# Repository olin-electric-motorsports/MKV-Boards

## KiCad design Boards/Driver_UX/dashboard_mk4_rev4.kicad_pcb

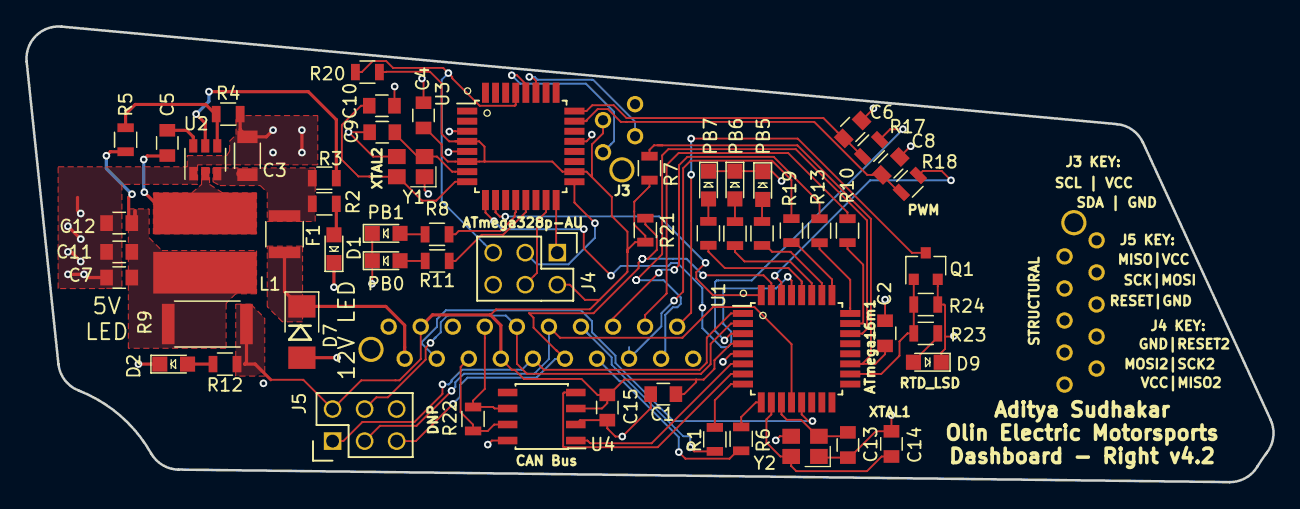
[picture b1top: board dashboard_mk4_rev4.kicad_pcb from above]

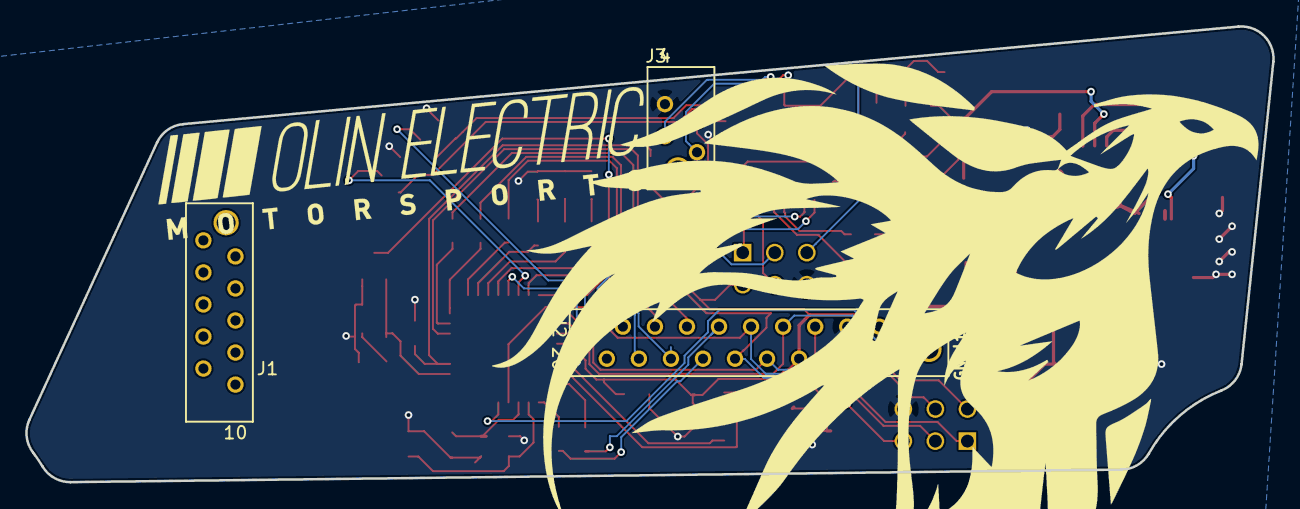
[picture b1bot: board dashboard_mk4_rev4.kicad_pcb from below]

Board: 2 copper layers, 98.8 x 36.1 mm, 62 parts (3 on the bottom side), 61 nets.

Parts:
C1, C4, C5, C6, C7, C8, C15: C_0.1uF; C_0805_OEM
C2: C_100pF; C_0805_OEM
C3: C_22uF; C_1206_OEM
C9, C10, C13, C14: C_30pF; C_0805_OEM
C11: C_1uF; C_0805_OEM
C12: C_47uF; C_0805_OEM
D1, D2: LED_0805; LED_0805_OEM
D7: D_Zener_18V; DO-214AA
D9: LED; LED_0805_OEM
F1: 500mA; Fuse_1210
J1: MM_F_VT_10; micromatch_female_vert_10
J2: MM_F_VT_20; micromatch_female_vert_20
J3: MM_F_VT_04; micromatch_female_vert_4
J4, J5: CONN_02X03; Pin_Header_Straight_2x03
L1: L_4.7uH; 4.7uH_Inductor_OEM
PB0, PB1, PB5, PB6, PB7: LED; LED_0805_OEM
Q1: SSM3K333R; SOT-23F
R1, R6, R8, R10, R11, R12, R13, R14, R15, R16, R19, R23: R_200; R_0805_OEM
R2: R_1k; R_0805_OEM
R3, R4, R21: R_10k; R_0805_OEM
R5: R_51.1k; R_0805_OEM
R7: R_100; R_0805_OEM
R9: R_0_Jumper; R_2512_OEM
R17, R18: R_100K; R_0805_OEM
R20: R_10K; R_0805_OEM
R22: R_120; R_0805_OEM
R24: R_100k; R_0805_OEM
U1: ATMEGA16M1; TQFP-32_7x7mm_Pitch0.8mm
U2: TPS561201; SOT-23-6_OEM
U3: ATmega328P-AU_FORMULA_MK4; TQFP-32_7x7mm_Pitch0.8mm
U4: CAN_Transceiver; SOIC-8_3.9x4.9mm_Pitch1.27mm_OEM
Y1, Y2: Crystal_SMD; Crystal_SMD_FA238

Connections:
+12V: D7.1, F1.1, J2.2
/12V_Fused: C3.1, F1.2, R2.1, R3.1, U2.3
/CANH: J2.6, R22.1, U4.7
/CANL: J2.7, R22.2, U4.6
/INFO1: U1.29, U3.9
/INFO2: U1.32, U3.10
/LED_BMS: J2.16, R19.2
/LED_IMD: J2.17, R10.1
/LED_START: J2.15, R13.1
/MISO: J2.10, J5.1, U1.1
/MISO_2: J4.1, U3.16
/MOSI: J2.9, J5.4, U1.2
/MOSI_2: J4.4, U3.15
/PWM_0: R18.1, U1.30
/PWM_1: R17.1, U1.3
/RESET: J2.12, J5.5, R21.1, U1.31
/RESET_2: J4.5, R20.1, U3.29
/RJLED1: J2.13, R1.1
/RJLED2: J2.14, R6.1
/RTD_BUZZER: J2.19, Q1.3
/RXCAN: U1.7, U4.4
/SCK: J2.11, J5.3, U1.12
/SCK_2: J4.3, U3.17
/SCL: J3.1, U3.28
/SDA: J3.2, U3.27
/START_BTN: J2.18, U1.22
/STR_POT_SENSE: J2.4, U1.13
/TXCAN: U1.6, U4.1
/XTAL1: C9.1, U3.7, Y1.1
/XTAL2: C10.1, U3.8, Y1.3
GND: C1.2, C2.2, C3.2, C4.2, C6.2, C7.2, C8.2, C9.2, C10.2, C11.2, C12.2, C13.2, C14.2, C15.2, D1.1, D2.1, D7.2, D9.1, J2.1, J2.5, J3.4, J4.6, J5.6, PB0.1, PB1.1, PB5.1, PB6.1, PB7.1, Q1.2, R4.2, R24.2, U1.5, U2.1, U3.3, U3.5, U3.21, U4.2, U4.8, Y1.2, Y1.4, Y2.2, Y2.4
unnamed: C2.1, R7.2, U1.19
unnamed: C5.1, U2.6
unnamed: C5.2, L1.1, U2.2
unnamed: C6.1, R17.2, U3.24
unnamed: C8.1, R18.2, U3.23
unnamed: C7.1, C11.1, C12.1, L1.2, R5.2, R9.2
unnamed: C13.1, U1.11, Y2.1
unnamed: C14.1, U1.10, Y2.3
unnamed: D1.2, R2.2
unnamed: D2.2, R12.2
unnamed: PB1.2, R8.1
unnamed: PB0.2, R11.1
unnamed: PB5.2, R14.2
unnamed: PB6.2, R15.2
unnamed: PB7.2, R16.2
unnamed: D9.2, R23.2
unnamed: Q1.1, R23.1, R24.1, U1.18
unnamed: R1.2, U1.8
unnamed: R3.2, U2.5
unnamed: R4.1, R5.1, U2.4
unnamed: R6.2, U1.9
unnamed: R8.2, U3.12
unnamed: R10.2, U1.23
unnamed: R11.2, U3.13
unnamed: R13.2, U1.24
unnamed: R14.1, U1.26
unnamed: R15.1, U1.27
unnamed: R16.1, U1.28
unnamed: R19.1, U1.25
VCC: C1.1, C4.1, C15.1, J2.3, J2.8, J3.3, J4.2, J5.2, R7.1, R9.1, R12.1, R20.2, R21.2, U1.4, U3.4, U3.6, U3.18, U4.3

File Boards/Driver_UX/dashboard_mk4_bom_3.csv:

Component,Description,Part,References,Value,Footprint,Quantity Per PCB,Datasheet,Package,MPN,MFN,PurchasingLink
1,"Capacitor, 0.1uF, 50V, 5%, 0805",C_0.1uF,C1 C4 C5 C6 C7 C8 C15,C_0.1uF,C_0805_OEM,7,http://datasheets.avx.com/X7RDielectric.pdf,Value,478-3352-1-ND,DK,https://www.digikey.com/products/en?keywords=478-3352-1-ND
2,"Capacitor, 100pF, 50V, 5%, 0805",C_100pF,C2,C_100pF,C_0805_OEM,1,https://katalog.we-online.de/pbs/datasheet/885012007057.pdf,Value,732-7852-1-ND,DK,https://www.digikey.com/product-detail/en/wurth-electronics-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
3,"Capacitor, 1uF, 25V, 10%, 0805",C_1uF,C11,C_1uF,C_0805_OEM,1,http://www.samsungsem.com/kr/support/product-search/mlcc/__i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,Value,1276-2887-1-ND,DK,https://www.digikey.com/product-detail/en/samsung-electro-me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
4,"Capacitor, 22uF, 16V, 20%, 1206",C_22uF,C3,C_22uF,C_1206_OEM,1,https://product.tdk.com/info/en/catalog/datasheets/mlcc_comm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,Value,445-11693-1-ND,DK,https://www.digikey.com/product-detail/en/tdk-corporation/C3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
5,"Capacitor, 30pF, 50V, 5%, 0805",C_30pF,C9 C10 C13 C14,C_30pF,C_0805_OEM,4,https://media.digikey.com/pdf/Data%20Sheets/Samsung%20PDFs/C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,Value,1276-1130-1-ND,DK,https://www.digikey.com/product-detail/en/samsung-electro-me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
6,"Capacitor, 47uF, 6.3V, 20%, 0805",C_47uF,C12,C_47uF,C_0805_OEM,1,http://www.samsungsem.com/kr/support/product-search/mlcc/__i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,Value,1276-6467-1-ND,DK,https://www.digikey.com/product-detail/en/samsung-electro-me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
7,"Diode, Zener, 18V, 5W, 5%",D_Zener_18V,D7,D_Zener_18V,DO-214AA,1,http://www.mccsemi.com/up_pdf/SMBJ5338B-SMBJ5388B(SMB).pdf,DO-214AA (SMB),SMBJ5355B-TPMSCT-ND,DK,https://www.digikey.com/products/en?keywords=SMBJ5355B-TPMSCT-ND
8,Light emitting diode,LED,D3 D4 D5 D6 D8,LED,LED_0805_OEM,5,,,,,
9,Light emitting diode,LED,D9,LED,LED_0805_OEM,1,~,,,,
10,"LED, Green, 2.2V, 20mA, 0805",LED_0805,D1 D2,LED_0805,LED_0805_OEM,2,http://www.osram-os.com/Graphics/XPic9/00078860_0.pdf,Value,475-1410-1-ND,DK,https://www.digikey.com/products/en?keywords=475-1410-1-ND
11,"Fuse, PTC, 500mA, 16V, 1210",F_500mA_16V,F1,500mA,Fuse_1210,1,https://belfuse.com/resources/CircuitProtection/datasheets/0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,Value,507-1786-1-ND,DK,https://www.digikey.com/product-detail/en/bel-fuse-inc/0ZCH0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
12,"Connector header through hole 2x3 0.100"" (2.54mm)",CONN_02X03,J4 J5,CONN_02X03,Pin_Header_Straight_2x03,2,http://portal.fciconnect.com/Comergent//fci/drawing/67996.pdf,Value,609-3234-ND,DK,https://www.digikey.com/product-detail/en/amphenol-fci/67997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
13,Micro-MaTch connector 4 pin female vertical,MM_F_VT_04,J3,MM_F_VT_04,micromatch_female_vert_4,1,http://www.te.com/commerce/DocumentDelivery/DDEController?Ac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,,338068-4,TE,http://www.te.com/global-en/product-338068-4.html
14,Micro-MaTch connector 10 pin female vertical,MM_F_VT_10,J1,MM_F_VT_10,micromatch_female_vert_10,1,http://www.te.com/commerce/DocumentDelivery/DDEController?Ac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,,1-338068-0,TE,http://www.te.com/global-en/product-1-338068-0.html
15,Micro-MaTch connector 20 pin female vertical,MM_F_VT_20,J2,MM_F_VT_20,micromatch_female_vert_20,1,http://www.te.com/commerce/DocumentDelivery/DDEController?Ac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,,2-338068-0,TE,http://www.te.com/global-en/product-2-338068-0.html
16,"Inductor, 4.7uH, 4.4A, 25mOhm, 20%",L_4.7uH,L1,L_4.7uH,4.7uH_Inductor_OEM,1,https://product.tdk.com/info/en/documents/wdcatalog/withdraw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,Value,445-6583-1-ND,DK,https://www.digikey.com/product-detail/en/tdk-corporation/VL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
17,"MOSFET, N-channel, 30V, 6A",SSM3K333R,Q1,SSM3K333R,SOT-23F,1,https://drive.google.com/drive/folders/0B-V-iZf33Y4GNzhDQTJZanJRbVk,,SSM3K333RLFCT-ND,DK,https://www.digikey.com/product-detail/en/toshiba-semiconduc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
18,"Resistor, 0 ohm jumper, 0.1W, 0603",R_0,R9,R_0_Jumper,R_0603_1608Metric,1,http://industrial.panasonic.com/www-cgi/jvcr13pz.cgi?E+PZ+3+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,Value,P0.0GCT-ND,DK,https://www.digikey.com/product-detail/en/panasonic-electron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
19,"Resistor, 100, 0.25W, 1%, 0805",R_100,R7,R_100,R_0805_OEM,1,https://www.seielect.com/Catalog/SEI-rncp.pdf,Value,RNCP0805FTD100RCT-ND,DK,https://www.digikey.com/products/en?keywords=RNCP0805FTD100RCT-ND
20,"Resistor, 100K, 0.125W, 1%, 0805",R_100K,R17 R18,R_100K,R_0805_OEM,2,https://industrial.panasonic.com/cdbs/www-data/pdf/RDA0000/A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,,P100KCCT-ND,DK,https://www.digikey.com/product-detail/en/panasonic-electron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
21,Resistor,R,R24,R_100k,R_0805_OEM,1,~,,,,
22,"Resistor, 10K, 0.25W, 1%, 0805",R_10K,R20 R21,R_10K,R_0805_OEM,2,http://www.bourns.com/data/global/pdfs/CRS.pdf,Value,CRS0805-FX-1002ELFCT-ND,DK,https://www.digikey.com/products/en?keywords=CRS0805-FX-1002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
23,"Resistor, 10K, 5W, 1%, Axial",R_10K_HV,R3 R4,R_10k,R_1K_HV,2,http://www.vishay.com/docs/28731/pacserie.pdf,Value,PPC5D10.0KCT-ND,DK,https://www.digikey.com/products/en?keywords=PPC5D10.0KCT-ND
24,"Resistor, 200, 0.125W, 5%, 0805",R_200,R22,R_120,R_0805_OEM,1,https://www.seielect.com/Catalog/SEI-RMCF_RMCP.pdf,Value,RMCF0805JT200RCT-ND,DK,https://www.digikey.com/products/en?keywords=RMCF0805JT200RCT-ND
25,"Resistor, 1K, 0.25W, 1%, 0805",R_1K,R2,R_1k,R_0805_OEM,1,https://www.seielect.com/Catalog/SEI-rncp.pdf,Value,RNCP0805FTD1K00CT-ND,DK,https://www.digikey.com/products/en?keywords=RNCP0805FTD1K00CT-ND
26,"Resistor, 200, 0.125W, 5%, 0805",R_200,R1 R6 R8 R10 R11 R12 R13 R14 R15 R16 R19,R_200,R_0805_OEM,11,https://www.seielect.com/Catalog/SEI-RMCF_RMCP.pdf,Value,RMCF0805JT200RCT-ND,DK,https://www.digikey.com/products/en?keywords=RMCF0805JT200RCT-ND
27,Resistor,R,R23,R_200,R_0805_OEM,1,~,,,,
28,"Resistor, 51.1K, 0.125W, 1%, 0805",R_51.1K,R5,R_51.1k,R_0805_OEM,1,https://industrial.panasonic.com/cdbs/www-data/pdf/RDA0000/A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,Value,P51.1KCCT-ND,DK,https://www.digikey.com/product-detail/en/panasonic-electron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
29,"Microcontroller, 8-bit, 1KB RAM, 16KB Flash",ATMEGA16M1,U1,ATMEGA16M1,TQFP-32_7x7mm_Pitch0.8mm,1,http://ww1.microchip.com/downloads/en/DeviceDoc/Atmel-8209-8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,,ATMEGA16M1-AU-ND,DK,https://www.digikey.com/product-detail/en/atmel/ATMEGA16M1-A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
30,"High speed CAN transceiver, 1Mb/s",MCP2561-E_SN,U4,CAN_Transceiver,SOIC-8_3.9x4.9mm_Pitch1.27mm_OEM,1,http://www.microchip.com/mymicrochip/filehandler.aspx?ddocna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,Value,MCP2561-E/SN-ND,DK,https://www.digikey.com/products/en?keywords=mcp2561-e%2Fsn
31,"Buck converter, 4.5-17V input, adj 0.76-7V output, 1A, 580kHz",TPS561201,U2,TPS561201,SOT-23-6_OEM,1,http://www.ti.com/lit/ds/symlink/tps561201.pdf,Value,TPS561201,DK,https://www.digikey.com/products/en?keywords=296-46928-1-ND
32,CRYSTAL 16.0000MHZ 18PF SMD,Crystal_SMD,Y1 Y2,Crystal_SMD,Crystal_SMD_FA238,2,http://www.txccorp.com/download/products/quartz_crystals/201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,Value,887-1125-1-ND,DK,https://www.digikey.com/product-detail/en/txc-corporation/7M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





Component Groups:,32
Component Count:,61
Fitted Components:,61
Number of PCBs:,1
Total components:,61
Schematic Version:,3
Schematic Date:,
BoM Date:,Sun 24 Feb 2019 12:24:09 PM EST
Schematic Source:,/home/asudhakar/Documents/Forumla/MKIV-Boards/Boards/Dashboard Mk4/rev4/dashboard_mk4.sch
KiCad Version:,Eeschema 5.0.2-bee76a0~70~ubuntu18.04.1

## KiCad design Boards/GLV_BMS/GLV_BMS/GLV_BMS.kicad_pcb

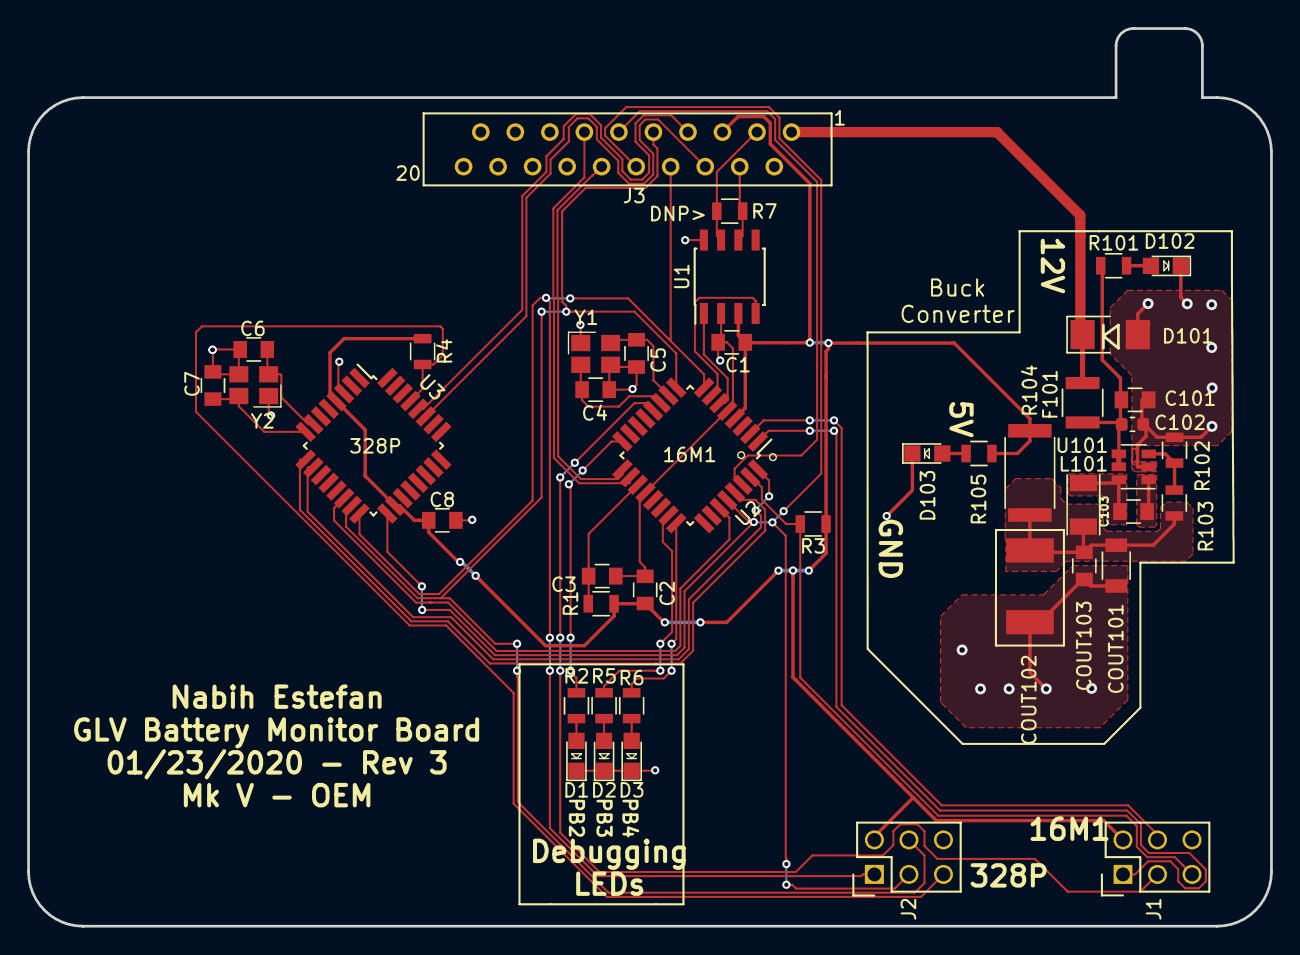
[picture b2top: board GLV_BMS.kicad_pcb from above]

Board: 2 copper layers, 91.4 x 66.0 mm, 43 parts (0 on the bottom side), 41 nets.

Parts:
C1, C2, C8, C101, C103: C_0.1uF; C_0805_OEM
C3: C_100pF; C_0805_OEM
C4, C5, C6, C7: C_30pF; C_0805_OEM
C102: C_2.2uF; C_0603_1608Metric
COUT101: C_22uF; C_1206_OEM
COUT102: C_33uF; Fuse_1812
COUT103: C_47uF; C_0805_OEM
D1, D2, D3, D102, D103: LED_0805; LED_0805_OEM
D101: D_Zener_18V; DO-214AA
F101: F_500mA_16V; Fuse_1210
J1, J2: CONN_02X03; Pin_Header_Straight_2x03
J3: MM_F_RA_20; micromatch_female_ra_20
L101: L_100uH; L_100uH_OEM
R1: R_100; R_0805_OEM
R2, R5, R6, R105: R_200; R_0805_OEM
R3, R4: R_10K; R_0805_OEM
R7: R_120_DNP; R_0805_OEM
R101: R_1K; R_0805_OEM
R102: R_25K; R_0805_OEM
R103: R_100K; R_0805_OEM
R104: R_0_2512; R_2512_OEM
U1: MCP2561-E_SN; SOIC-8_3.9x4.9mm_Pitch1.27mm_OEM
U2: ATMEGA16M1; TQFP-32_7x7mm_Pitch0.8mm
U3: ATmega328P-AU; TQFP-32_7x7mm_P0.8mm
U101: TPS560430YF; SOT-23-6_OEM
Y1, Y2: Crystal_SMD; Crystal_SMD_FA238

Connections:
+12V: D101.1, F101.2, J3.1
/ALERT_COOLING: J3.13, U2.18
/ALERT_GLV: J3.12, U2.17
/CAN_HI: J3.3, R7.1, U1.7
/CAN_LO: J3.4, R7.2, U1.6
/CAN_RX: U1.4, U2.7
/CAN_TX: U1.1, U2.6
/CS_2: U2.27, U3.14
/CS_GLV: J3.11, U2.30
/INFO1: U2.29, U3.9
/INFO2: U2.32, U3.10
/LED_1: R2.2, U2.16
/LED_2: R5.2, U2.23
/LED_3: R6.2, U2.24
/MISO: J1.1, U2.1
/MISO_2: J2.1, J3.8, U2.8, U3.16
/MOSI: J1.4, U2.2
/MOSI_2: J2.4, J3.9, U2.9, U3.15
/RESET: J1.5, R3.2, U2.31
/RESET_2: J2.5, R4.2, U3.29
/SCK: J1.3, U2.12
/SCK_2: J2.3, J3.10, U2.28, U3.17
/SCL: J3.7, U3.28
/SDA: J3.6, U3.27
/XTAL1: C4.1, U2.11, Y1.1
/XTAL1_2: C6.1, U3.7, Y2.1
/XTAL2: C5.1, U2.10, Y1.3
/XTAL2_2: C7.1, U3.8, Y2.3
GND: C1.2, C2.2, C3.2, C4.2, C5.2, C6.2, C7.2, C8.2, C101.2, C102.2, COUT101.2, COUT102.2, COUT103.2, D1.1, D2.1, D3.1, D101.2, D102.1, D103.1, J1.6, J2.6, J3.2, J3.14, J3.15, J3.16, J3.17, J3.18, J3.19, J3.20, R102.2, U1.2, U1.8, U2.5, U2.20, U3.3, U101.2, Y1.2, Y1.4, Y2.2, Y2.4
unnamed: C3.1, R1.2, U2.19
unnamed: C101.1, C102.1, F101.1, R101.1, U101.4, U101.5
unnamed: C103.1, U101.1
unnamed: C103.2, L101.1, U101.6
unnamed: COUT101.1, COUT102.1, COUT103.1, L101.2, R103.1, R104.1
unnamed: D1.2, R2.1
unnamed: D2.2, R5.1
unnamed: D3.2, R6.1
unnamed: D102.2, R101.2
unnamed: D103.2, R105.2
unnamed: R102.1, R103.2, U101.3
VCC: C1.1, C2.1, C8.1, J1.2, J2.2, J3.5, R1.1, R3.1, R4.1, R104.2, R105.1, U1.3, U2.4, U3.4, U3.18

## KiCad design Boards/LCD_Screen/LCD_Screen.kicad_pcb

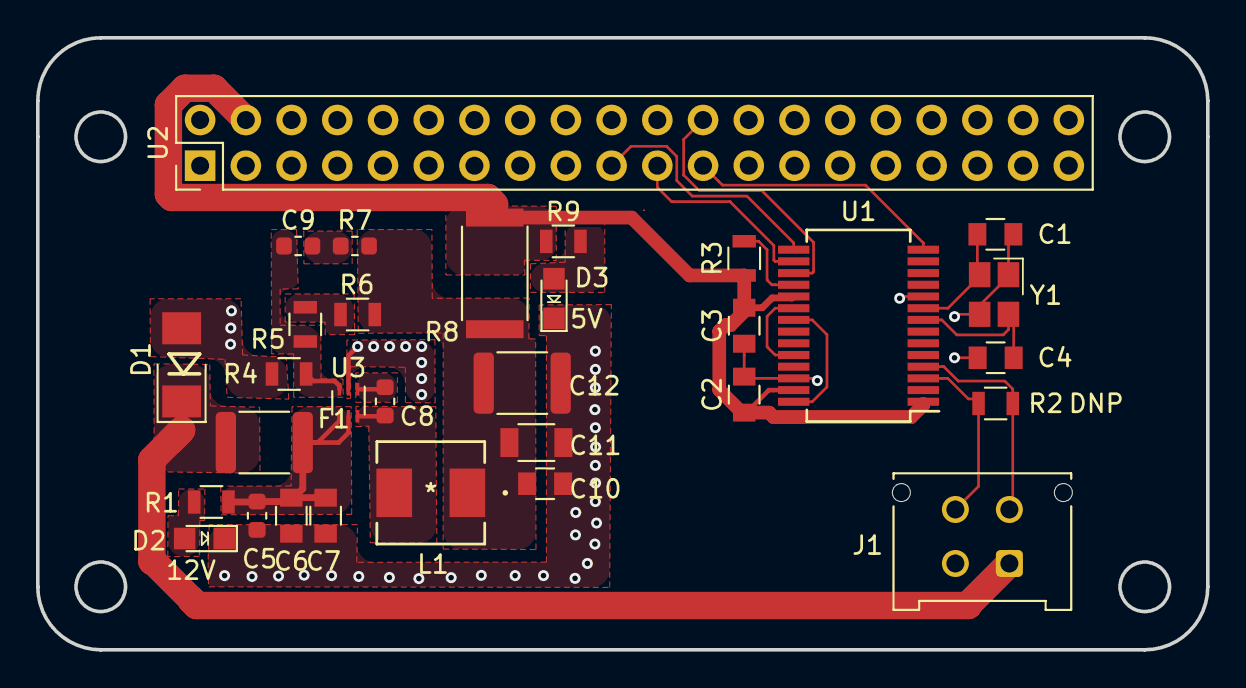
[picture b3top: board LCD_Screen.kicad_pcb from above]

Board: 2 copper layers, 65.0 x 34.0 mm, 31 parts (0 on the bottom side), 23 nets.

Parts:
C1, C4: C_30pF; C_0805_OEM
C2: C_0.1uF; C_0805_OEM
C3: C_100pF; C_0805_OEM
C5: C_0.1uF; C_0603_1608Metric
C6, C7: C_10uF_25V; C_0805_OEM
C8: C_0.1uF_0603; C_0603_1608Metric
C9: C_100nF; C_0603_1608Metric
C10: C_10uF; C_0805_OEM
C11: C_22uF; C_1206_OEM
C12: C_33uF; C_1812_4532Metric
D1: D_Zener_18V; DO-214AA
D2, D3: LED_0805; LED_0805_OEM
F1: F_2.6A_16V; Fuse_1812_4532Metric
J1: MicroFit_VT_4
L1: L_4.7uH_3.2A; IHLP2020BZER4R7M11
R1: R_1K; R_0805_OEM
R2: R_120_DNP; R_0805_OEM
R3, R4: R_10K; R_0805_OEM
R5: R_51.1K; R_0805_OEM
R6: R_22K; R_0805_OEM
R7: R_1; R_0603_1608Metric
R8: R_0_2512; R_2512_OEM
R9: R_200; R_0805_OEM
U1: MCP25625-x-SS; SSOP-28_5.3x10.2mm_P0.65mm
U2: Raspberry_Pi_Zero; PinHeader_2x20_P2.54mm_Vertical
U3: TPS563231; SOT-563
Y1: Crystal_SMD; Crystal_SMD_FA238

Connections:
/12V: D1.1, F1.1, J1.1
/CANH: J1.3, R2.1, U1.4
/CANL: J1.4, R2.2, U1.3
/MISO: U1.16, U2.21
/MOSI: U1.15, U2.19
/SCK: U1.14, U2.23
/~CS~: U1.17, U2.24
GND: C1.2, C2.2, C3.2, C4.2, C5.2, C6.2, C7.2, C10.2, C11.2, C12.2, D1.2, D2.1, D3.1, J1.2, R4.2, U1.10, U1.26, U2.39, U3.2, Y1.2, Y1.4
unnamed: C1.1, U1.9, Y1.1
unnamed: C4.1, U1.8, Y1.3
unnamed: C5.1, C6.1, C7.1, F1.2, R1.1, U3.4, U3.5
unnamed: C8.1, L1.2, U3.6
unnamed: C8.2, U3.1
unnamed: C9.1, R4.1, R5.2, U3.3
unnamed: C9.2, R7.1
unnamed: C10.1, C11.1, C12.1, L1.1, R6.1, R7.2, R8.2
unnamed: D2.2, R1.2
unnamed: D3.2, R9.2
unnamed: R3.1, U1.18
unnamed: R5.1, R6.2
unnamed: U1.20, U1.24
unnamed: U1.21, U1.28
VCC: C2.1, C3.1, R3.2, R8.1, R9.1, U1.1, U1.19, U1.27, U2.4

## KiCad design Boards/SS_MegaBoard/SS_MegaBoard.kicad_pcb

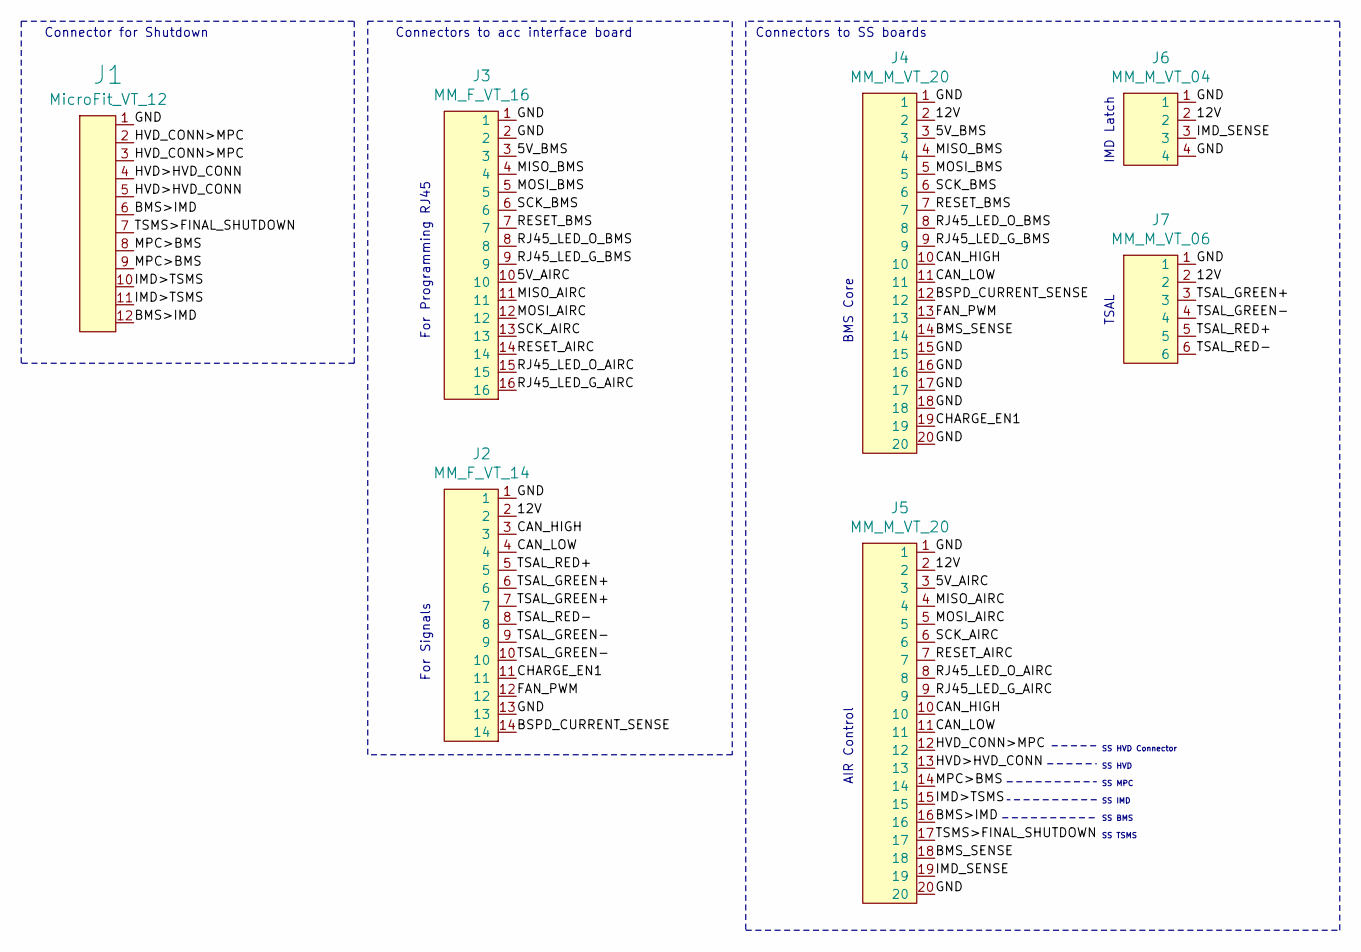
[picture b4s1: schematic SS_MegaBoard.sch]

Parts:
J1: MicroFit_VT_12
J2: MM_F_VT_14; micromatch_female_vert_14; MPN 1-338068-4
J3: MM_F_VT_16; micromatch_female_vert_16; MPN 1-338068-6
J4, J5: MM_M_VT_20; micromatch_female_vert_20; MPN 2-215464-0
J6: MM_M_VT_04; micromatch_female_vert_4; MPN 215464-4
J7: MM_M_VT_06; micromatch_female_vert_6; MPN 215464-6

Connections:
/5V_AIRC: J3.10, J5.3
/5V_BMS: J3.3, J4.3
/12V: J2.2, J4.2, J5.2, J6.2, J7.2
/BMS>IMD: J1.6, J1.12, J5.16
/BMS_SENSE: J4.14, J5.18
/BSPD_CURRENT_SENSE: J2.14, J4.12
/CAN_HIGH: J2.3, J4.10, J5.10
/CAN_LOW: J2.4, J4.11, J5.11
/CHARGE_EN1: J2.11, J4.19
/FAN_PWM: J2.12, J4.13
/GND: J1.1, J2.1, J2.13, J3.1, J3.2, J4.1, J4.15, J4.16, J4.17, J4.18, J4.20, J5.1, J5.20, J6.1, J6.4, J7.1
/HVD>HVD_CONN: J1.4, J1.5, J5.13
/HVD_CONN>MPC: J1.2, J1.3, J5.12
/IMD>TSMS: J1.10, J1.11, J5.15
/IMD_SENSE: J5.19, J6.3
/MISO_AIRC: J3.11, J5.4
/MISO_BMS: J3.4, J4.4
/MOSI_AIRC: J3.12, J5.5
/MOSI_BMS: J3.5, J4.5
/MPC>BMS: J1.8, J1.9, J5.14
/RESET_AIRC: J3.14, J5.7
/RESET_BMS: J3.7, J4.7
/RJ45_LED_G_AIRC: J3.16, J5.9
/RJ45_LED_G_BMS: J3.9, J4.9
/RJ45_LED_O_AIRC: J3.15, J5.8
/RJ45_LED_O_BMS: J3.8, J4.8
/SCK_AIRC: J3.13, J5.6
/SCK_BMS: J3.6, J4.6
/TSAL_GREEN+: J2.6, J2.7, J7.3
/TSAL_GREEN-: J2.9, J2.10, J7.4
/TSAL_RED+: J2.5, J7.5
/TSAL_RED-: J2.8, J7.6
/TSMS>FINAL_SHUTDOWN: J1.7, J5.17

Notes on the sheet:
BMS Core
AIR Control
IMD Latch
TSAL
Connectors to SS boards
Connectors to acc interface board
Connector for Shutdown
For Programming RJ45
For Signals
SS HVD Connector SS HVD SS MPC SS IMD SS BMS SS TSMS

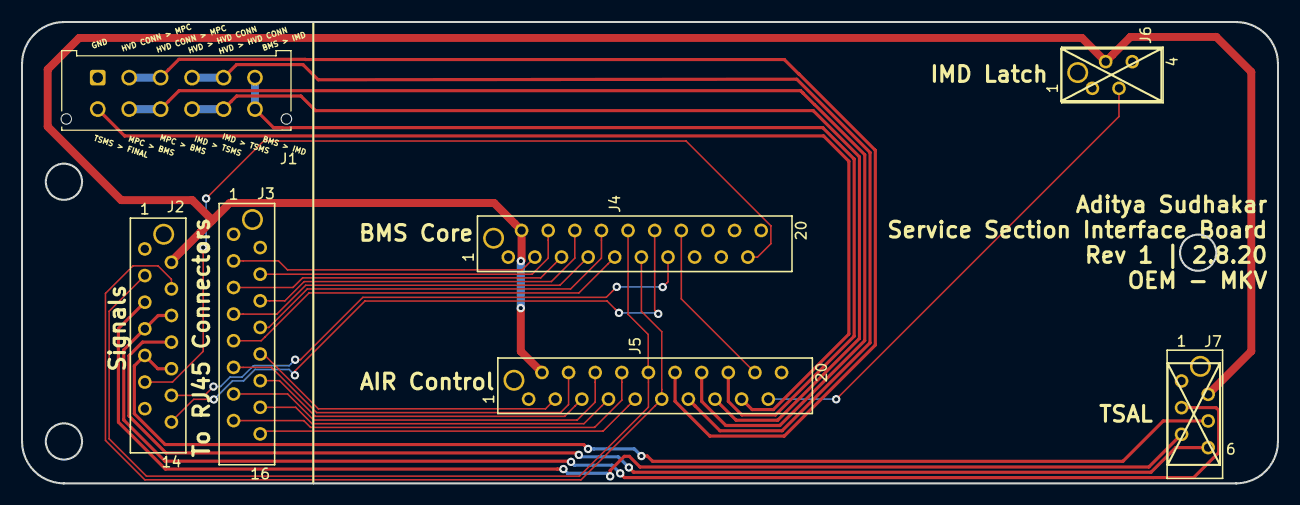
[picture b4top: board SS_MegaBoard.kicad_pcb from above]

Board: 2 copper layers, 119.8 x 44.0 mm, 7 parts (0 on the bottom side), 33 nets.

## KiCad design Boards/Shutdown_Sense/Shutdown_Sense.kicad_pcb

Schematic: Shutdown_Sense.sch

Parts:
C1, C9, C101, C103: C_0.1uF; C_0805_OEM; MPN 478-3352-1-ND
C2: C_100pF; C_0805_OEM; MPN 399-1122-1-ND
C3, C4: C_30pF; C_0805_OEM; MPN 1276-1130-1-ND
C102: C_2.2uF; C_0603; MPN 311-1451-1-ND
COUT101: C_22uF; C_1206_OEM; MPN 445-11693-1-ND
COUT102: C_33uF; Fuse_1812; MPN 445-3924-1-ND
COUT103: C_47uF; C_0805_OEM; MPN 1276-6467-1-ND
D2, D3, D4, D5, D6, D7, D8, D9, D10, D11, D12, D13, D102, D103: LED_0805; LED_0805_OEM; MPN 475-1410-1-ND
D101: D_Zener_18V; DO-214AA; MPN SMBJ5355B-TPMSCT-ND
F101: F_500mA_16V; Fuse_1210; MPN 507-1786-1-ND
IC1: ATMEGA16M1; TQFP-32_7x7mm_Pitch0.8mm; MPN ATMEGA16M1-AU-ND
J2: MM_F_RA_20; micromatch_female_ra_20; MPN 2-338070-0
J3: CONN_02X03; Pin_Header_Straight_2x03; MPN 609-3234-ND
L101: L_100uH; MPN 445-15759-1-ND
Q3, Q4: SSM3K333R; SOT-23F; MPN SSM3K333RLFCT-ND
R1: R_100; R_0805_OEM; MPN RNCP0805FTD100RCT-ND
R2: R_120_DNP; R_0805_OEM; MPN 667-ERJ-6ENF1200V
R3: R_10k; R_0805_OEM; MPN CRS0805-FX-1002ELFCT-ND
R5, R6, R7, R8, R9, R10, R11, R12, R13, R14, R105: R_200; R_0805_OEM; MPN RMCF0805JT200RCT-ND
R21, R26, R101: R_1K; R_0805_OEM; MPN RNCP0805FTD1K00CT-ND
R22, R29, R103: R_100K; R_0805_OEM; MPN P100KCCT-ND
R23, R31: R_10K; R_0805_OEM; MPN CRS0805-FX-1002ELFCT-ND
R102: R_25K; R_0805_OEM; Digi-key Part Number CPF-A-0805B25KE
R104: R_0_2512; R_2512_OEM; MPN A121322CT-ND
TP1, TP2, TP3: Test_Point_SMD
U3: CAN_Transceiver; SOIC-8_3.9x4.9mm_Pitch1.27mm_OEM; MPN MCP2561-E/SN-ND
U101: TPS560430YF; SOT-23-6_OEM; MPN TPS560430YFDBVR
Y1: Crystal_SMD; Crystal_SMD_FA238; MPN SER3686CT-ND

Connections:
+12V: F101.2, J2.2, TP1.1
/CAN_high: J2.3, R2.1, U3.7 (CANH)
/CAN_low: J2.4, R2.2, U3.6 (CANL)
/DEBUG_LED_1: IC1.13 ((PCINT21/ADC2/ACMP2)PD5); also elsewhere on the board
/MISO: IC1.1 ((PCINT18/PSCIN2/OC1A/MISO_A)PD2), J3.1
/MOSI: IC1.2 ((PCINT19/TXD/TXLIN/OC0A/~SS~/MOSI_A)PD3), J3.4
/RESET: IC1.31 ((PCINT24/OCD/~RESET~)PE0), J3.5, R3.2
/RXCAN: IC1.7 ((PCINT11/T1/ICP1B/RXCAN)PC3), U3.4 (RXD)
/SCK: IC1.12 ((PCINT20/ADC1/RXD/RXLIN/ICP1A/SCK_A)PD4), J3.3
/SS_BMS: IC1.30 ((PCINT8/INT3/PSCOUT1A)PC0), R7.2
/SS_BOTS: IC1.25 ((PCINT15/D2A/AMP2+)PC7), R12.2
/SS_BSPD: IC1.23 ((PCINT3/AMP0-)PB3), R14.2
/SS_Connector_2_HVD: IC1.28 ((PCINT7/ADC4/SCK/PSCOUT0B)PB7), R9.2
/SS_Crash_Sensor: IC1.24 ((PCINT4/AMP0+)PB4), R13.2
/SS_ESTOP: J2.5, Q4.1 (G), R26.1, R29.1
/SS_ESTOP_Driver: IC1.26 ((PCINT5/ADC6/INT2/ACMPN1/AMP2-)PB5), R11.2
/SS_GLVMS: J2.6, Q3.1 (G), R21.1, R22.1
/SS_HVD: IC1.27 ((PCINT6/ADC7/PSCOUT1B)PB6), R10.2
/SS_IMD: IC1.32 ((PCINT17/CLKO/PSCIN0)PD1), R6.2
/SS_Main_Pack_Connector: IC1.29 ((PCINT16/PSCOUT0A)PD0), R8.2
/SS_TSMS: IC1.3 ((PCINT9/PSCIN1/OC1B/~SS_A~)PC1), R5.2
/TXCAN: IC1.6 ((PCINT10/T0/TXCAN)PC2), U3.1 (TXD)
GND: C1.2, C2.2, C3.2, C4.2, C9.2, C101.2, C102.2, COUT101.2, COUT102.2, COUT103.2, D2.1 (K), D3.1 (K), D4.1 (K), D5.1 (K), D6.1 (K), D7.1 (K), D8.1 (K), D9.1 (K), D10.1 (K), D11.1 (K), D12.1 (K), D13.1 (K), D101.2 (A), D102.1 (K), D103.1 (K), IC1.5 (GND), IC1.20 (AGND), J2.1, J2.7, J2.8, J2.9, J2.10, J2.11, J2.12, J2.13, J2.14, J2.15, J2.16, J2.17, J2.18, J2.19, J2.20, J3.6, Q3.2 (S), Q4.2 (S), R22.2, R29.2, R102.2, TP2.1, U3.2 (VSS), U3.8 (STBY), U101.2 (GND), Y1.2, Y1.4; also elsewhere on the board
unnamed: C2.1, IC1.19 (AVCC), R1.2
unnamed: C3.1, IC1.11 ((PCINT26/ADC0/XTAL2)PE2), Y1.1
unnamed: C4.1, IC1.10 ((PCINT25/OC0B/XTAL1)PE1), Y1.3
unnamed: C101.1, C102.1, D101.1 (K), F101.1, R101.1, U101.4 (EN), U101.5 (VIN)
unnamed: C103.1, L101.1, U101.6 (SW)
unnamed: C103.2, U101.1 (CB)
unnamed: COUT101.1, COUT102.1, COUT103.1, L101.2, R103.1, R104.1
unnamed: D2.2 (A), R5.1
unnamed: D3.2 (A), R6.1
unnamed: D4.2 (A), R7.1
unnamed: D5.2 (A), R8.1
unnamed: D6.2 (A), R9.1
unnamed: D7.2 (A), R21.2
unnamed: D8.2 (A), R26.2
unnamed: D9.2 (A), R10.1
unnamed: D10.2 (A), R11.1
unnamed: D11.2 (A), R12.1
unnamed: D12.2 (A), R13.1
unnamed: D13.2 (A), R14.1
unnamed: D102.2 (A), R101.2
unnamed: D103.2 (A), R105.2
unnamed: R102.1, R103.2, U101.3 (FB)
VCC: C1.1, C9.1, IC1.4 (VCC), J3.2, R1.1, R3.1, R23.1, R31.1, R104.2, R105.1, TP3.1, U3.3 (VDD)

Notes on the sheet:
Atmega 16 (Main Microcontroller)
Shutdown Circuit Nodes
Input Capacitors
12V Indicator
Protection
BUCK CONVERTER
Feedback Divider
Inductor
Bootstrap Capacitor
Output Capacitors
VCC Jumper
5V Indicator

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
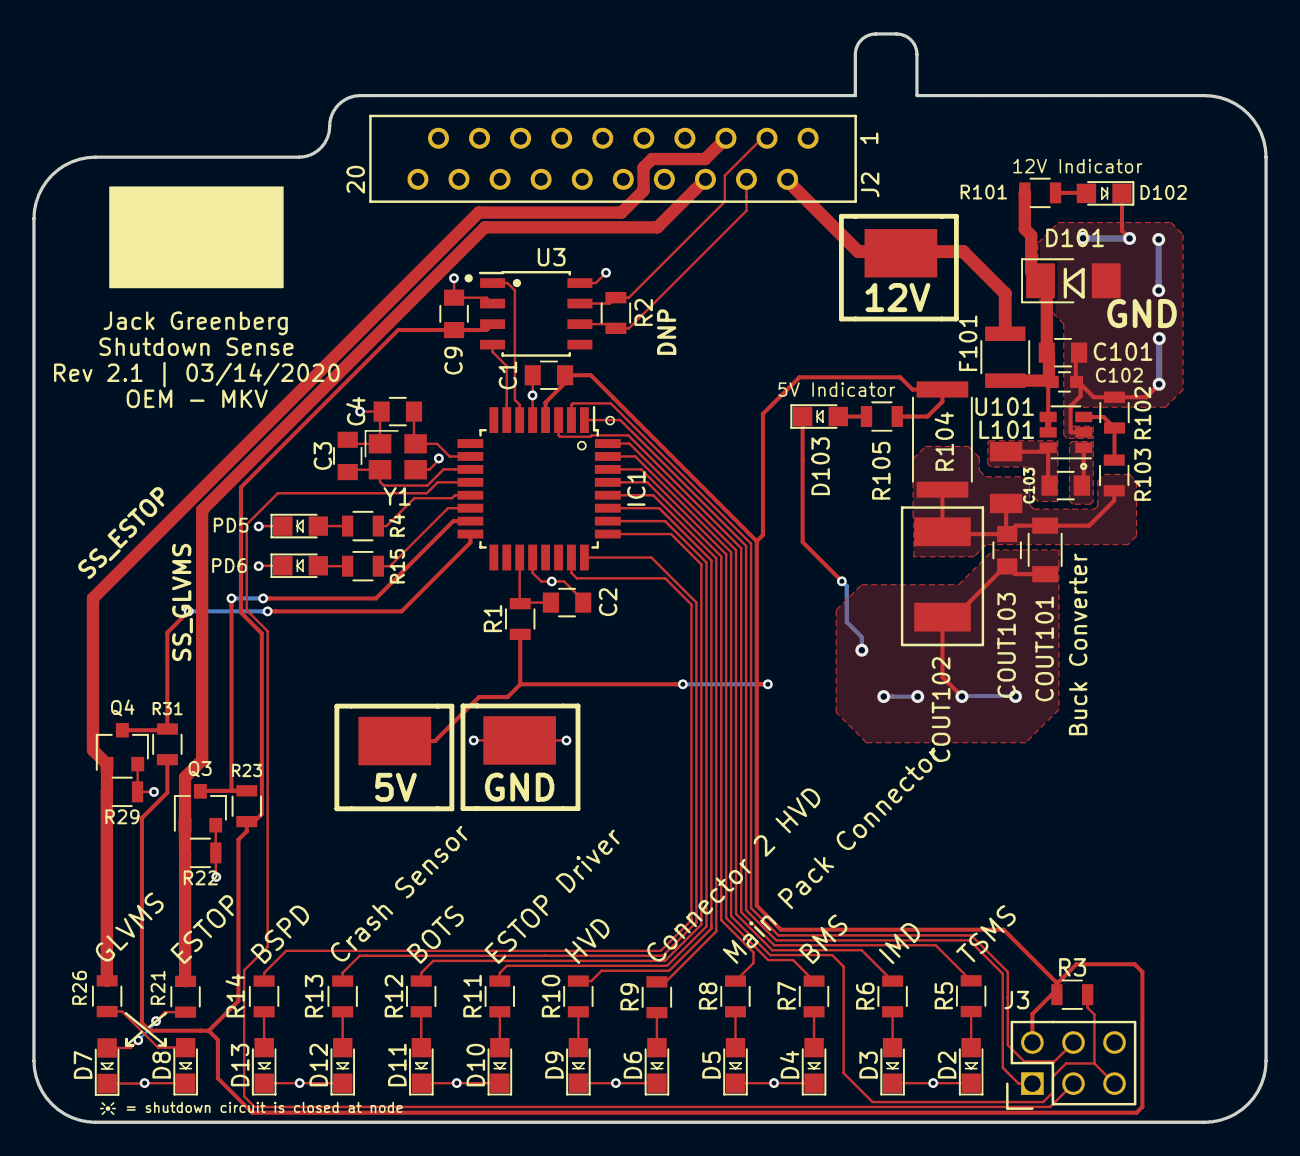
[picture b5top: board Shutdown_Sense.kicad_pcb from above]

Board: 2 copper layers, 76.2 x 67.3 mm, 67 parts (0 on the bottom side), 51 nets.

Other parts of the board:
PD5, PD6: LED_0805; LED_0805_OEM
R4, R15: R_200; R_0805_OEM

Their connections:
/DEBUG_LED_1: R4.1; also elsewhere on the board
GND: PD5.1, PD6.1; also elsewhere on the board
unnamed: PD5.2, R4.2
unnamed: PD6.2, R15.2

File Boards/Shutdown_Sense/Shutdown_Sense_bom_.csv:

Component,Description,Part,References,Value,Footprint,Quantity Per PCB,Datasheet,Package,MPN,MFN,PurchasingLink,Link,Digi-key Part Number,Purchasing Link
1,"Capacitor, 0.1uF, 50V, 5%, 0805",C_0.1uF,C1 C9 C101 C103,C_0.1uF,C_0805_OEM,4,http://datasheets.avx.com/X7RDielectric.pdf,Value,478-3352-1-ND,Digi-Key DK,https://www.digikey.com/products/en?keywords=478-3352-1-ND,,,
2,"Capacitor, 100pF, 50V, 5%, 0805",C_100pF,C2,C_100pF,C_0805_OEM,1,https://content.kemet.com/datasheets/KEM_C1003_C0G_SMD.pdf,Value,399-1122-1-ND,Digi-Key,https://www.digikey.com/product-detail/en/kemet/C0805C101J5G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,,,
3,"Capacitor, 2.2uF, 10V, 10%, 0603",C_2.2uF,C102,C_2.2uF,C_0603,1,http://www.yageo.com/documents/recent/UPY-GPHC_X5R_4V-to-50V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,,311-1451-1-ND,DK,https://www.digikey.com/product-detail/en/yageo/CC0603KRX5R6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,,,
4,"Capacitor, 30pF, 50V, 5%, 0805",C_30pF,C3 C4,C_30pF,C_0805_OEM,2,https://media.digikey.com/pdf/Data%20Sheets/Samsung%20PDFs/C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,Value,1276-1130-1-ND,Digi-Key,https://www.digikey.com/product-detail/en/samsung-electro-me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,,,
5,"Capacitor, 22uF, 16V, 20%, 1206",C_22uF,COUT101,C_22uF,C_1206_OEM,1,https://product.tdk.com/info/en/catalog/datasheets/mlcc_comm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,,445-11693-1-ND,DK,https://www.digikey.com/product-detail/en/tdk-corporation/C3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,,,
6,,C_33uF,COUT102,C_33uF,Fuse_1812,1,https://product.tdk.com/info/en/catalog/datasheets/mlcc_comm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,,445-3924-1-ND,C4532X7R1C336M250KC,https://www.digikey.com/product-detail/en/tdk-corporation/C4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,,,
7,"Capacitor, 47uF, 6.3V, 20%, 0805",C_47uF,COUT103,C_47uF,C_0805_OEM,1,http://www.samsungsem.com/kr/support/product-search/mlcc/__i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,,1276-6467-1-ND,DK,https://www.digikey.com/product-detail/en/samsung-electro-me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,,,
8,"Diode, Zener, 18V, 5W, 5%",D_Zener_18V,D101,D_Zener_18V,DO-214AA,1,http://www.mccsemi.com/up_pdf/SMBJ5338B-SMBJ5388B(SMB).pdf,,SMBJ5355B-TPMSCT-ND,DK,https://www.digikey.com/products/en?keywords=SMBJ5355B-TPMSCT-ND,,,
9,"LED, Green, 2.2V, 20mA, 0805",LED_0805,D1 D2 D3 D4 D5 D6 D7 D8 D9 D10 D11 D12 D13 D102 D103,LED_0805,LED_0805_OEM,15,http://www.osram-os.com/Graphics/XPic9/00078860_0.pdf,,475-1410-1-ND,DK,https://www.digikey.com/products/en?keywords=475-1410-1-ND,,,
10,"Fuse, PTC, 500mA, 16V, 1210",F_500mA_16V,F101,F_500mA_16V,Fuse_1210,1,https://belfuse.com/resources/CircuitProtection/datasheets/0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,,507-1786-1-ND,DK,https://www.digikey.com/product-detail/en/bel-fuse-inc/0ZCH0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,,,
11,"Microcontroller, 8-bit, 1KB RAM, 16KB Flash",ATMEGA16M1,IC1,ATMEGA16M1,TQFP-32_7x7mm_Pitch0.8mm,1,http://www.atmel.com/Images/Atmel-8209-8-bit%20AVR%20ATmega1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,Value,ATMEGA16M1-AU-ND,Digi-Key,https://www.digikey.com/product-detail/en/atmel/ATMEGA16M1-A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,,,
12,"Connector header through hole 2x3 0.100"" (2.54mm)",CONN_02X03,J3,CONN_02X03,Pin_Header_Straight_2x03,1,http://portal.fciconnect.com/Comergent//fci/drawing/67996.pdf,Value,609-3234-ND,Digi-Key,https://www.digikey.com/product-detail/en/amphenol-fci/67997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,,,
13,Micro-MaTch connector 20 pin female right angle,MM_F_RA_20,J2,MM_F_RA_20,micromatch_female_ra_20,1,http://www.te.com/commerce/DocumentDelivery/DDEController?Ac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,,2-338070-0,TE,http://www.te.com/usa-en/product-2-338070-0.html,,,
14,,L_100uH,L101,L_100uH,L_100uH,1,https://product.tdk.com/info/en/catalog/datasheets/inductor_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,,445-15759-1-ND,Digikey,,https://www.digikey.com/product-detail/en/tdk-corporation/NL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,,
15,"MOSFET, N-channel, 30V, 6A",SSM3K333R,Q3 Q4,SSM3K333R,SOT-23F,2,https://drive.google.com/drive/folders/0B-V-iZf33Y4GNzhDQTJZanJRbVk,,SSM3K333RLFCT-ND,DK,https://www.digikey.com/product-detail/en/toshiba-semiconduc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,,,
16,"Resistor, 0 ohm jumper, 3W, 2512",R_0_2512,R104,R_0_2512,R_2512_OEM,1,http://www.te.com/commerce/DocumentDelivery/DDEController?Ac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,,A121322CT-ND,DK,https://www.digikey.com/products/en?keywords=A121322CT-ND,,,
17,"Resistor, 100, 0.25W, 1%, 0805",R_100,R1,R_100,R_0805_OEM,1,https://www.seielect.com/Catalog/SEI-rncp.pdf,Value,RNCP0805FTD100RCT-ND,Digi-Key,https://www.digikey.com/products/en?keywords=RNCP0805FTD100RCT-ND,,,
18,"Resistor, 100K, 0.125W, 1%, 0805",R_100K,R22 R29 R103,R_100K,R_0805_OEM,3,https://industrial.panasonic.com/cdbs/www-data/pdf/RDA0000/A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,,P100KCCT-ND,DK,https://www.digikey.com/product-detail/en/panasonic-electron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,,,
19,"Resistor, 10K, 0.25W, 1%, 0805",R_10K,R3 R23 R31,R_10k,R_0805_OEM,3,http://www.bourns.com/data/global/pdfs/CRS.pdf,Value,CRS0805-FX-1002ELFCT-ND,Digi-Key DK,https://www.digikey.com/products/en?keywords=CRS0805-FX-1002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,,,
20,"Resistor, 120, 0.125W, 1%, 0805",R_120_DNP,R2,R_120_DNP,R_0805_OEM,1,https://www.mouser.com/datasheet/2/315/AOA0000C304-1149620.pdf,,667-ERJ-6ENF1200V,DK,https://www.mouser.com/ProductDetail/Panasonic-Industrial-De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,,,
21,"Resistor, 1K, 0.25W, 1%, 0805",R_1K,R21 R26 R101,R_1K,R_0805_OEM,3,https://www.seielect.com/Catalog/SEI-rncp.pdf,,RNCP0805FTD1K00CT-ND,DK,https://www.digikey.com/products/en?keywords=RNCP0805FTD1K00CT-ND,,,
22,"Resistor, 200, 0.125W, 5%, 0805",R_200,R4 R5 R6 R7 R8 R9 R10 R11 R12 R13 R14 R105,R_200,R_0805_OEM,12,https://www.seielect.com/Catalog/SEI-RMCF_RMCP.pdf,,RMCF0805JT200RCT-ND,DK,https://www.digikey.com/products/en?keywords=RMCF0805JT200RCT-ND,,,
23,,R_25K,R102,R_25K,R_0805_OEM,1,https://www.te.com/commerce/DocumentDelivery/DDEController?A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,,,A124124CT-ND,https://www.digikey.com/product-detail/en/te-connectivity-pa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,,CPF-A-0805B25KE,
24,"High speed CAN transceiver, 1Mb/s",MCP2561-E_SN,U3,CAN_Transceiver,SOIC-8_3.9x4.9mm_Pitch1.27mm_OEM,1,http://www.microchip.com/mymicrochip/filehandler.aspx?ddocna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,Value,MCP2561-E/SN-ND,Digi-Key,https://www.digikey.com/products/en?keywords=mcp2561-e%2Fsn,,,
25,,TPS560430YF,U101,TPS560430YF,SOT-23-6_OEM,1,http://www.ti.com/lit/ds/symlink/tps560430.pdf,,TPS560430YFDBVR,TPS560430YFDBVR-ND,,,,https://www.digikey.com/product-detail/en/texas-instruments/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
26,CRYSTAL 16.0000MHZ 18PF SMD,Crystal_SMD,Y1,Crystal_SMD,Crystal_SMD_FA238,1,https://support.epson.biz/td/api/doc_check.php?dl=brief_FA-2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,Value,SER3686CT-ND,Digi-Key,https://www.digikey.com/products/en?keywords=SER3686CT-ND,,,





Component Groups:,26
Component Count:,62
Fitted Components:,62
Number of PCBs:,1
Total components:,62
Schematic Version:,
Schematic Date:,
PCB Variant:,default
BoM Date:,Thu 12 Dec 2019 08:19:18 PM EST
Schematic Source:,/home/jgreenberg/Documents/Formula/MKV-Boards/Boards/Shutdown_Sense/Shutdown_Sense.sch
KiCad Version:,Eeschema 5.1.5-52549c5~84~ubuntu18.04.1

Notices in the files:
parts and their libraries:
Copyright 2016 Accelerated Designs. All rights reserved.
